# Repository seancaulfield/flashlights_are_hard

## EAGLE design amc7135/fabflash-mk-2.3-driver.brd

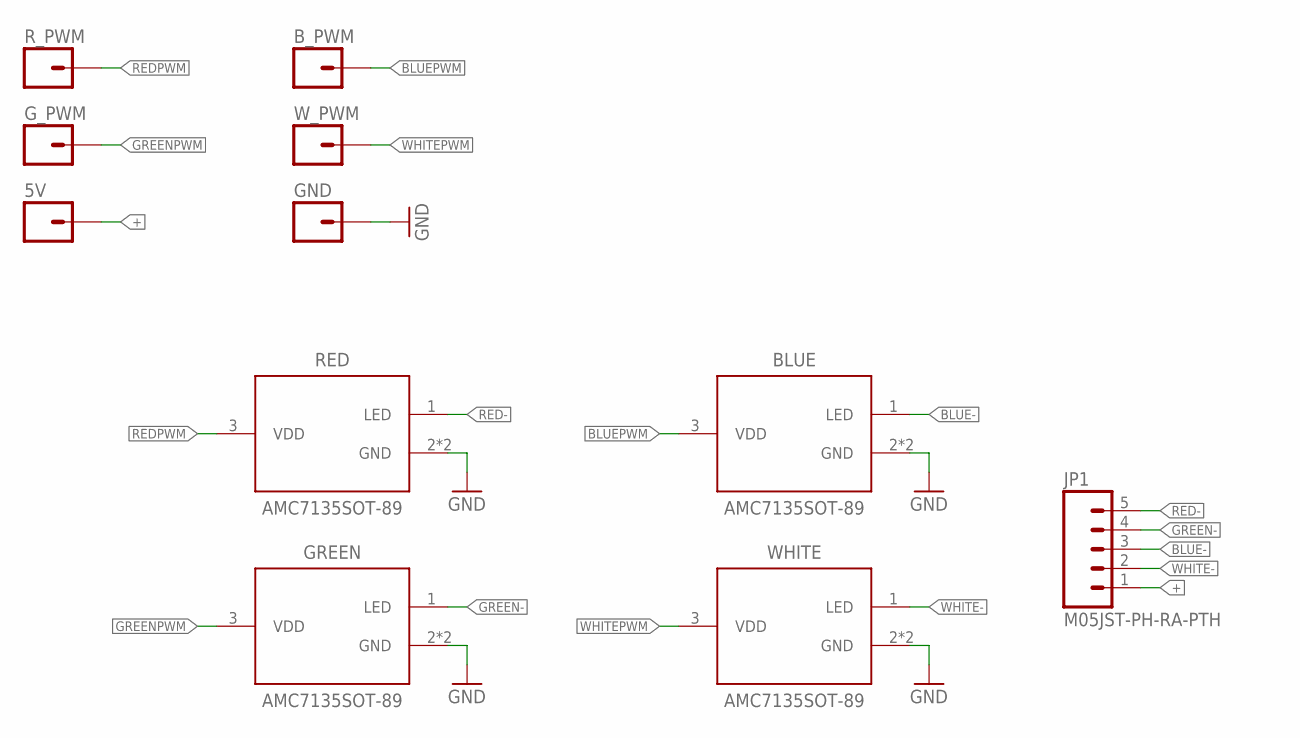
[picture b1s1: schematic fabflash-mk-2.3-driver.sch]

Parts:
5V: M01PTH-0.9MM; 1X01-0.9MM
BLUE: AMC7135SOT-89; SOT89
B_PWM: M01PTH-0.9MM; 1X01-0.9MM
GND: M01PTH-0.9MM; 1X01-0.9MM
GREEN: AMC7135SOT-89; SOT89
G_PWM: M01PTH-0.9MM; 1X01-0.9MM
JP1: M05JST-PH-RA-PTH; JST-5-PH-RA-PTH
RED: AMC7135SOT-89; SOT89
R_PWM: M01PTH-0.9MM; 1X01-0.9MM
WHITE: AMC7135SOT-89; SOT89
W_PWM: M01PTH-0.9MM; 1X01-0.9MM

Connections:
+: 5V.1, JP1.1
BLUE-: BLUE.1 (LED), JP1.3
BLUEPWM: BLUE.3 (VDD), B_PWM.1
GND: BLUE.2 (GND), BLUE.4 (GND), GND.1, GREEN.2 (GND), GREEN.4 (GND), RED.2 (GND), RED.4 (GND), WHITE.2 (GND), WHITE.4 (GND)
GREEN-: GREEN.1 (LED), JP1.4
GREENPWM: GREEN.3 (VDD), G_PWM.1
RED-: JP1.5, RED.1 (LED)
REDPWM: RED.3 (VDD), R_PWM.1
WHITE-: JP1.2, WHITE.1 (LED)
WHITEPWM: WHITE.3 (VDD), W_PWM.1

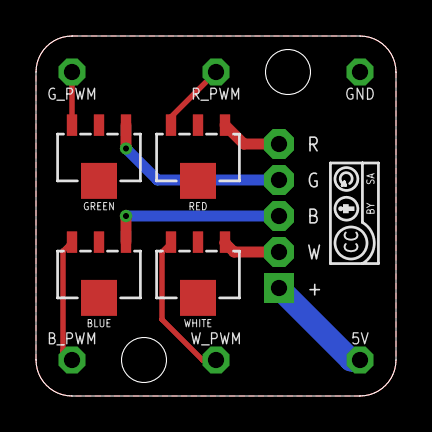
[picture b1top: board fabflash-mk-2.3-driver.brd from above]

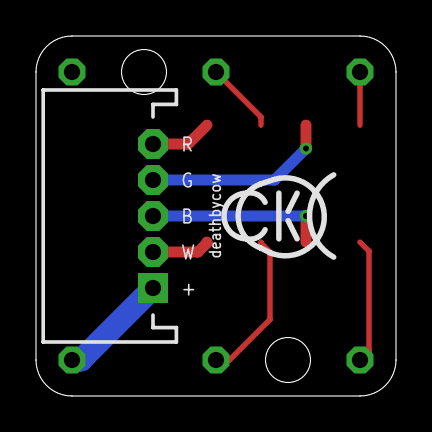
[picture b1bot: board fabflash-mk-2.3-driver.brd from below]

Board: 2 copper layers, 20.0 x 20.0 mm, 13 parts (2 on the bottom side), 10 nets.

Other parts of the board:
U$1: CC-BY-SA-4.0-NO-URL
U$2: COW_SMALL

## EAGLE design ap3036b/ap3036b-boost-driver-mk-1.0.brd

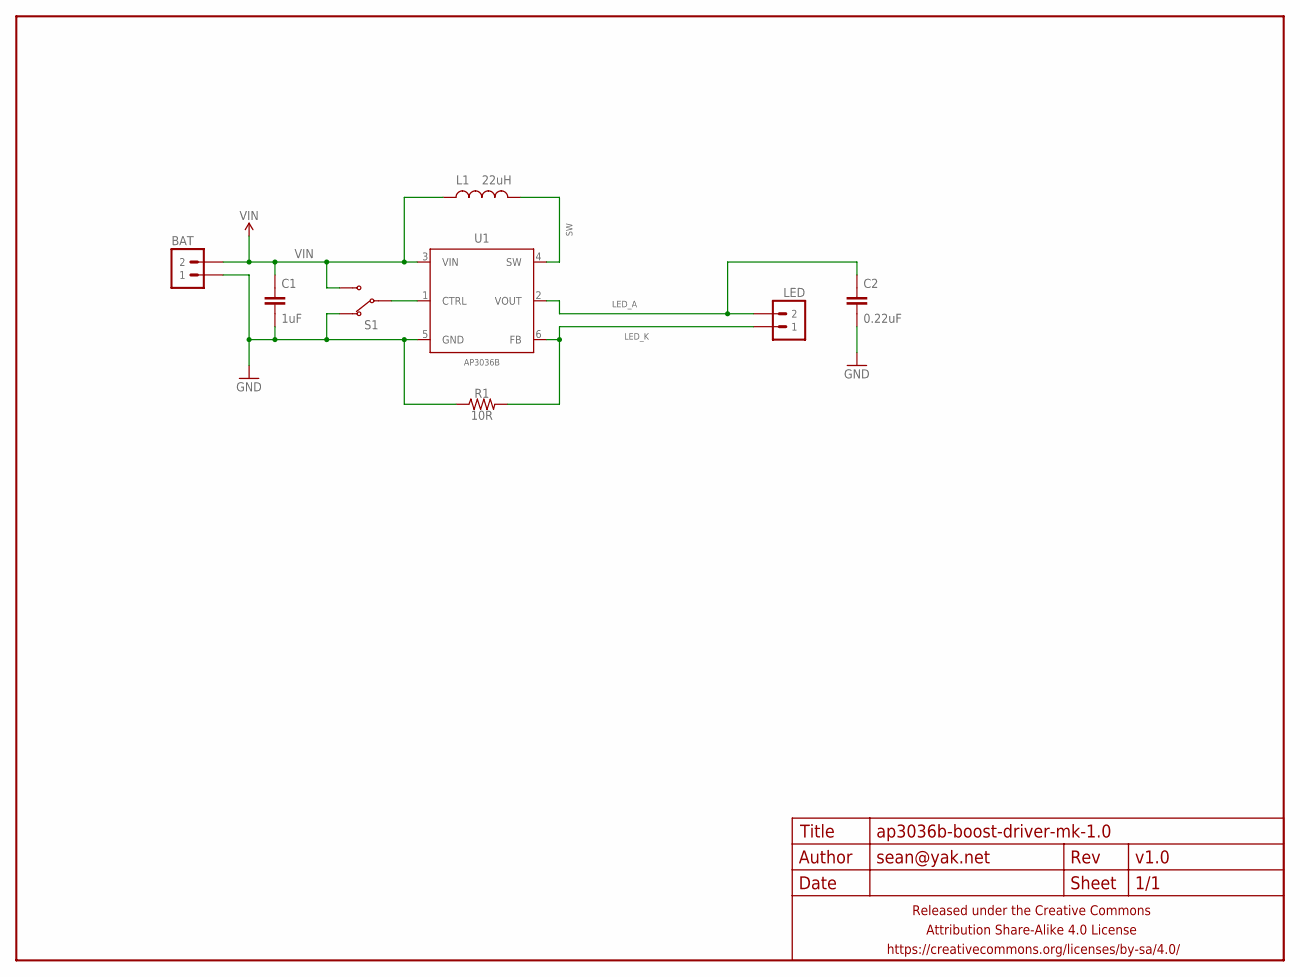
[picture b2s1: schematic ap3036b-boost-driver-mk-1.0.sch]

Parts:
BAT: M02PTH-CENTERED; 1X02-CENTER
C1: 1uF; C0603-TIGHTER
C2: 0.22uF; C0603-TIGHTER
FRAME1: FRAME-LETTERNO_PACKAGE; DUMMY
L1: 22uH; L0603
LED: M02PTH-CENTERED; 1X02-CENTER
R1: 10R; R0603-TIGHTER
S1: SWITCH-SPDTJS102011SAQN; SWITCH-SPDT-SMD-RA-JS102011SAQN
U1: AP3036B; SOT26

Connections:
GND: BAT.1, C1.2, C2.2, R1.1, S1.3 (NC), U1.5 (GND)
LED_A: C2.1, LED.2, U1.2 (VOUT)
LED_K: LED.1, R1.2, U1.6 (FB)
unnamed: S1.2 (COM), U1.1 (CTRL)
SW: L1.2, U1.4 (SW)
VIN: BAT.2, C1.1, L1.1, S1.1 (NO), U1.3 (VIN)

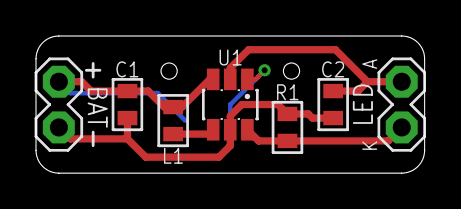
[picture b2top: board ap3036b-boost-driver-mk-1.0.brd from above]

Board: 2 copper layers, 21.6 x 7.6 mm, 9 parts (1 on the bottom side), 6 nets.

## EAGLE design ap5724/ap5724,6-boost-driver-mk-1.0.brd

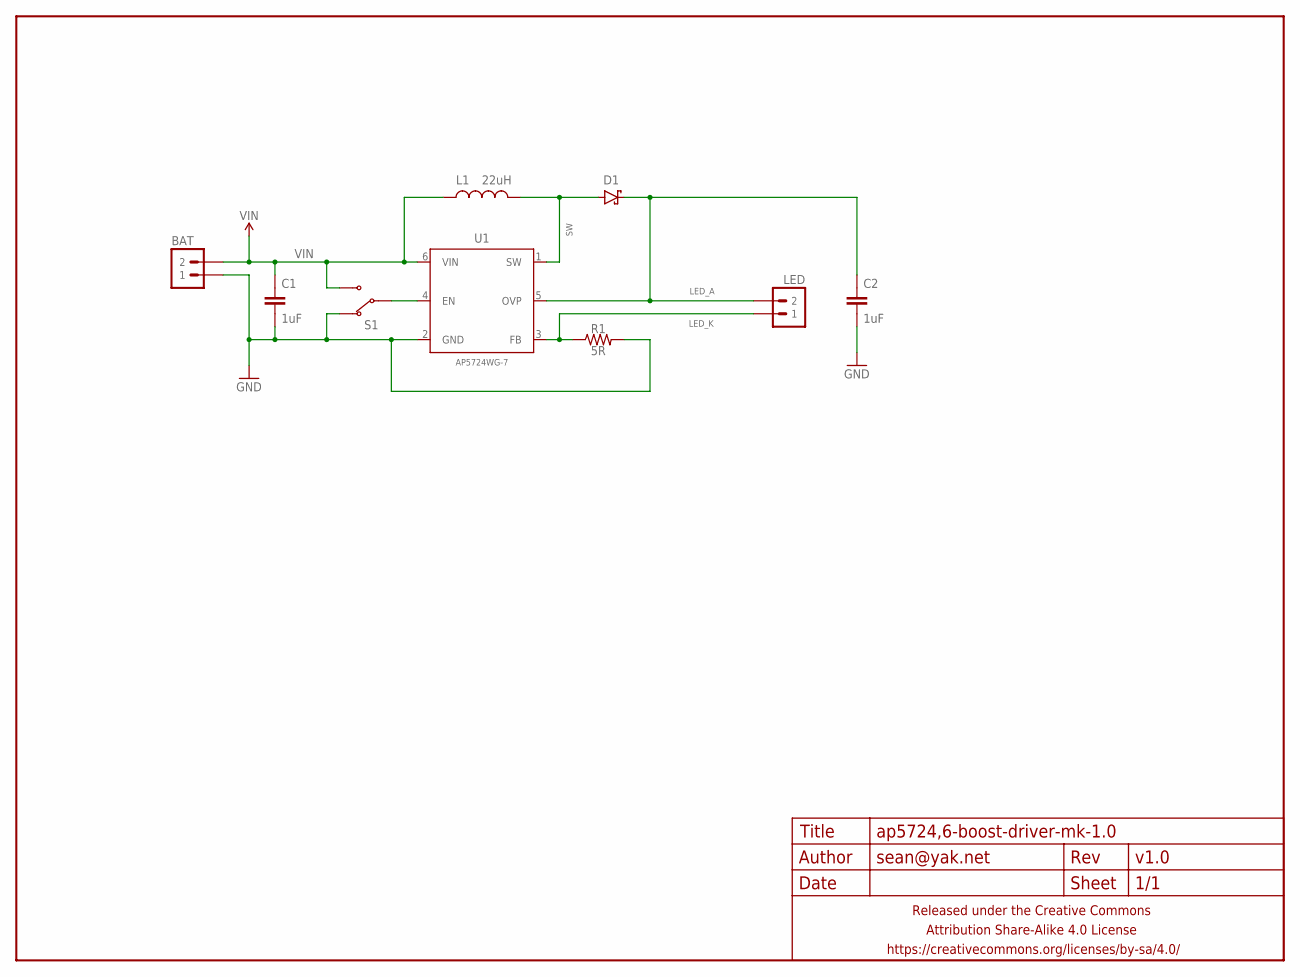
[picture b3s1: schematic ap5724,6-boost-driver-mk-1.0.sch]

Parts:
BAT: M02PTH-CENTERED; 1X02-CENTER
C1, C2: 1uF; C0603-TIGHTER
D1: DIODE-SCHOTTKYSOD323; SOD323-SCHOTTKY
FRAME1: FRAME-LETTERNO_PACKAGE; DUMMY
L1: 22uH; L0603
LED: M02PTH-CENTERED; 1X02-CENTER
R1: 5R; R0603-TIGHTER
S1: SWITCH-SPDTJS102011SAQN; SWITCH-SPDT-SMD-RA-JS102011SAQN
U1: AP5724WG-7; SOT26

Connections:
GND: BAT.1, C1.2, C2.2, R1.2, S1.3 (NC), U1.2 (GND)
LED_A: C2.1, D1.C, LED.2, U1.5 (OVP)
LED_K: LED.1, R1.1, U1.3 (FB)
unnamed: S1.2 (COM), U1.4 (EN)
SW: D1.A, L1.2, U1.1 (SW)
VIN: BAT.2, C1.1, L1.1, S1.1 (NO), U1.6 (VIN)

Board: 2 copper layers, 10 parts (1 on the bottom side), 6 nets, no tracks yet.

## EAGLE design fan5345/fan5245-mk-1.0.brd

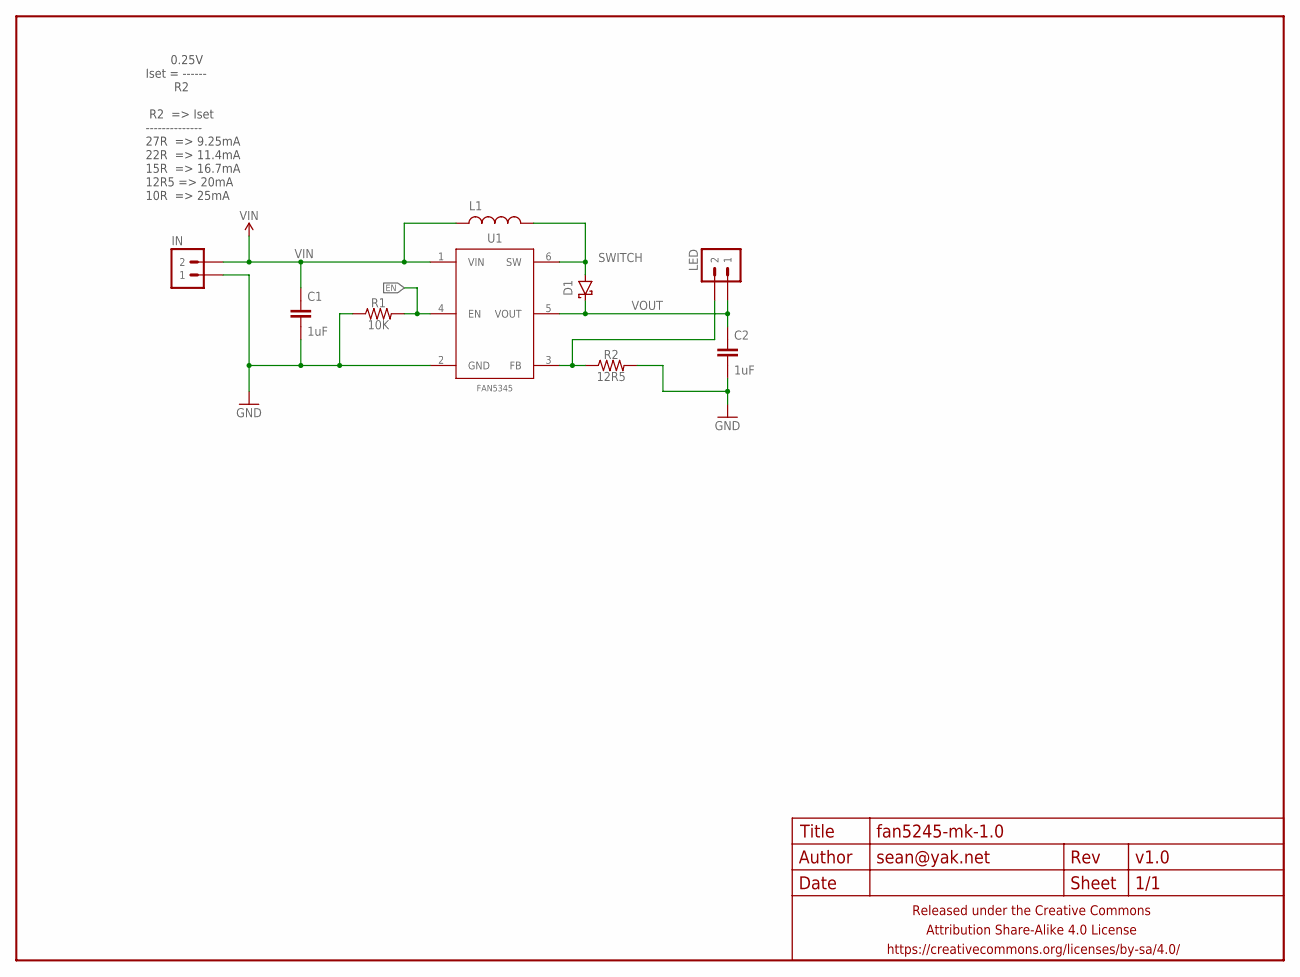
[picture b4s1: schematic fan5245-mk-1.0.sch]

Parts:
C1, C2: 1uF; C0603-TIGHTER
D1: DIODE-SCHOTTKYSOD323; SOD323-SCHOTTKY
FRAME1: FRAME-LETTERNO_PACKAGE; DUMMY
IN: M02PTH-CENTERED-R+; 1X02-CENTER-R+
L1: 10uH; L0603
LED: M02PTH-CENTERED-L+; 1X02-CENTER-L+
R1: 10K; R0603-TIGHTER
R2: 12R5; R0603-TIGHTER
U1: FAN5345; SOT23-6

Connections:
EN: R1.2, U1.4 (EN)
GND: C1.2, C2.2, IN.1, R1.1, R2.2, U1.2 (GND)
unnamed: LED.2, R2.1, U1.3 (FB)
SWITCH: D1.A, L1.2, U1.6 (SW)
VIN: C1.1, IN.2, L1.1, U1.1 (VIN)
VOUT: C2.1, D1.C, LED.1, U1.5 (VOUT)

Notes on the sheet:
0.25V Iset = ------ R2 R2 => Iset -------------- 27R => 9.25mA 22R => 11.4mA 15R => 16.7mA 12R5 => 20mA 10R => 25mA

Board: 2 copper layers, 10 parts (0 on the bottom side), 6 nets, no tracks yet.

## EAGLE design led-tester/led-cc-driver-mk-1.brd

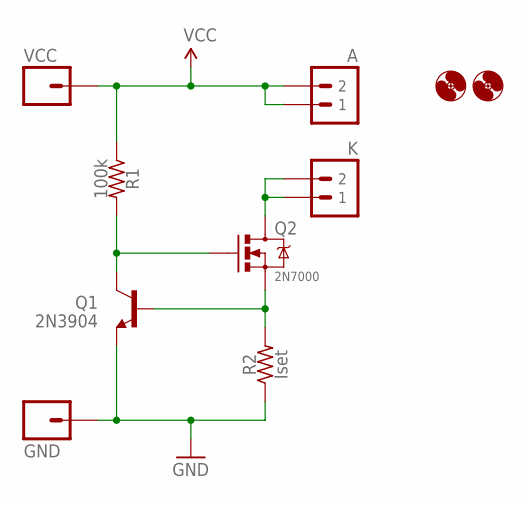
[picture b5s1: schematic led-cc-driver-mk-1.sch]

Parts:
A: M02PTH; 1X02
GND: M01PTH; 1X01
H1, H2: HOLE#2; HOLE-#2
K: M02PTH; 1X02
Q1: 2N3904; TO-92-AMMO
Q2: 2N7000; TO-92-AMMO
R1: 100k; RESISTOR-AXIAL-PTH-7.62MM
R2: Iset; RESISTOR-AXIAL-PTH-7.62MM
VCC: M01PTH; 1X01

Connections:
GND: GND.1, Q1.1 (E), R2.P$1 (1)
unnamed: Q1.2 (B), Q2.1 (S), R2.P$2 (2)
unnamed: Q1.3 (C), Q2.2 (G), R1.P$2 (2)
unnamed: K.1, K.2, Q2.3 (D)
VCC: A.1, A.2, R1.P$1 (1), VCC.1

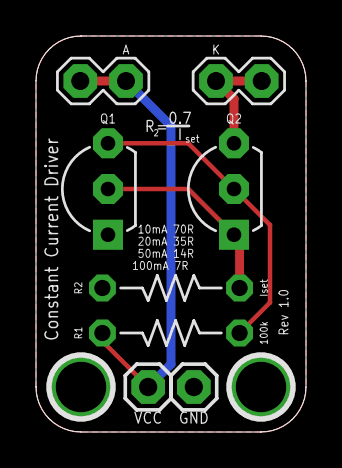
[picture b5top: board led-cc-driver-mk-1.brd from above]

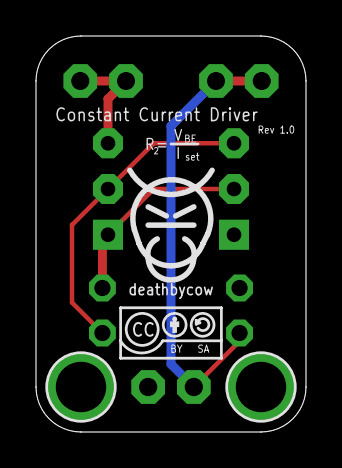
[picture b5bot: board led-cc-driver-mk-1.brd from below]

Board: 2 copper layers, 15.0 x 22.0 mm, 12 parts (2 on the bottom side), 5 nets.

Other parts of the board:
U$1: COW_SMALL
U$4: CC-BY-SA-4.0-NO-URL

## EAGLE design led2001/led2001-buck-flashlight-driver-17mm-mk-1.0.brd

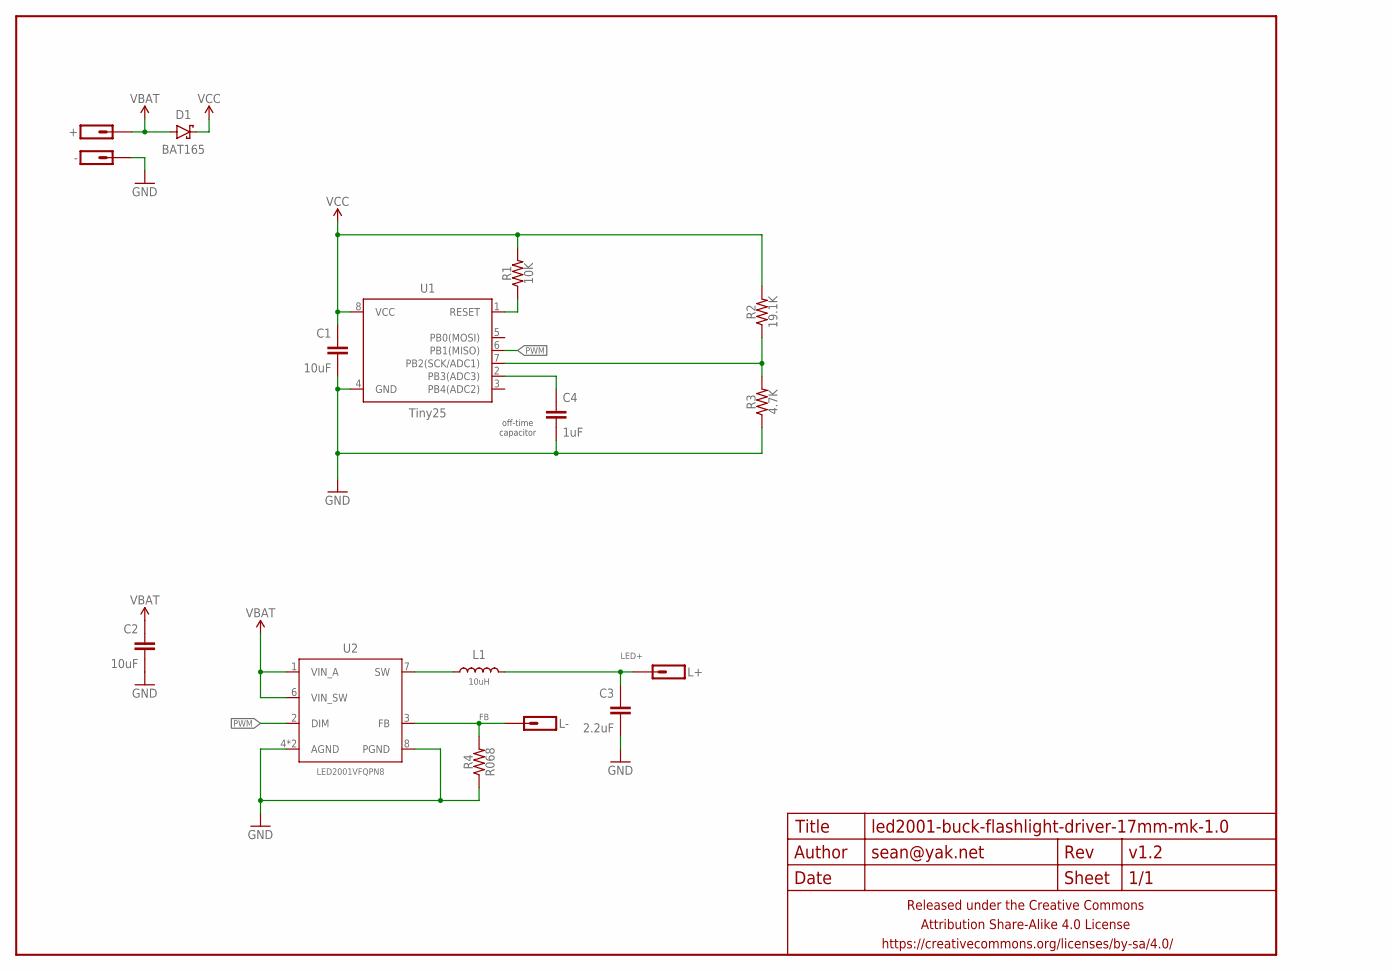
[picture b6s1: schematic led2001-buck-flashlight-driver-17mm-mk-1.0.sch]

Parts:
+: M01PTH-1MM-CIR-NS; 1X01-1MM-CIR-NS
-: M01NOT-A-VIA-NOPE; 1X01_NOSILK_NOSTOP
C1, C2: 10uF; C0603-TIGHTER
C3: 2.2uF; C0603-TIGHTER
C4: 1uF; C0402
D1: BAT165; SOD323-SCHOTTKY
FRAME1: FRAME-LETTERNO_PACKAGE; DUMMY
L1: 10uH; XAL40X0
L+: M01PTH-1MM-CIR-NS; 1X01-1MM-CIR-NS
L-: M01PTH-1MM-CIR-NS; 1X01-1MM-CIR-NS
R1: 10K; R0402
R2: 19.1K; R0603-TIGHTER
R3: 4.7K; R0603-TIGHTER
R4: R068; R0805-TIGHTER
U1: Tiny25; SO08-SKINNYPADS
U2: LED2001VFQPN8; VFQFPN8-4X4

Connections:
FB: L-.1, R4.2, U2.3 (FB)
GND: -.P$1, C1.2, C2.2, C3.2, C4.2, R3.1, R4.1, U1.4 (GND), U2.4 (AGND), U2.8 (PGND), U2.9 (AGND)
LED+: C3.1, L1.P$2 (2), L+.1
unnamed: L1.P$1 (1), U2.7 (SW)
unnamed: R1.1, U1.1 (RESET)
unnamed: R2.1, R3.2, U1.7 (PB2(SCK/ADC1))
unnamed: C4.1, U1.2 (PB3(ADC3))
PWM: U1.6 (PB1(MISO)), U2.2 (DIM)
VBAT: +.1, C2.1, D1.A, U2.1 (VIN_A), U2.6 (VIN_SW)
VCC: C1.1, D1.C, R1.2, R2.2, U1.8 (VCC)

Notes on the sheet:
off-time capacitor

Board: 2 copper layers, 17 parts (3 on the bottom side), 10 nets, no tracks yet.

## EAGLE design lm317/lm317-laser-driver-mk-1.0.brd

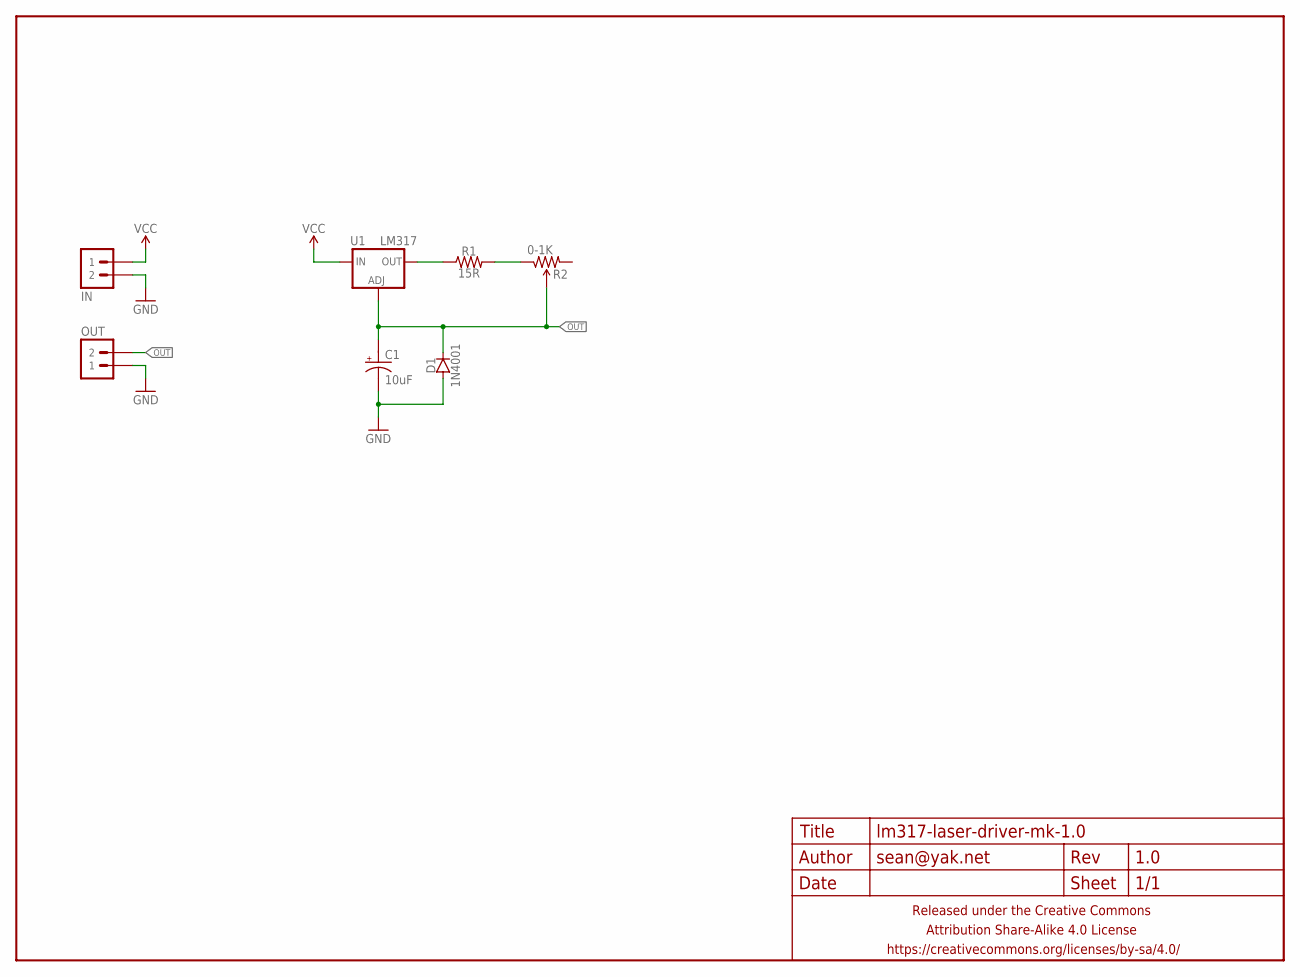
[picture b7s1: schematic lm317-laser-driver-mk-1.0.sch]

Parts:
C1: 10uF; E2,5-6
D1: 1N4001; DIODE-10.16MM-NOSYMBOL
FRAME1: FRAME-LETTERNO_PACKAGE; DUMMY
IN: M02PTH-CENTERED-R+; 1X02-CENTER-R+
OUT: M02PTH-CENTERED-R+; 1X02-CENTER-R+
R1: 15R; RESISTOR-AXIAL-PTH-10.16MM
R2: 0-1K; TRIM_POT_PTH2
U1: LM317; TO220-THERMPAD

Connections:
GND: C1.-, D1.A, IN.2, OUT.1
unnamed: R1.P$2 (2), R2.1 (CCW)
unnamed: R1.P$1 (1), U1.2@1 (OUT), U1.2@2 (OUT)
OUT: C1.+, D1.C, OUT.2, R2.2 (WIPER), U1.1 (ADJ)
VCC: IN.1, U1.3 (IN)

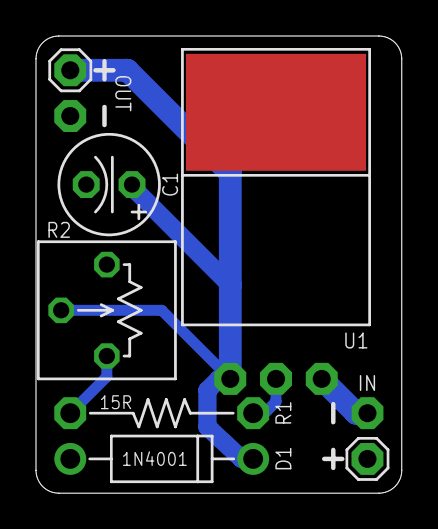
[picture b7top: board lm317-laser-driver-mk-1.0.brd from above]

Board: 2 copper layers, 20.3 x 25.4 mm, 9 parts (1 on the bottom side), 5 nets.

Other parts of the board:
U$1: COW

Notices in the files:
parts and their libraries:
a_parts: Released under the Creative Commons Attribution Share-Alike 4.0 License
a_parts: https://creativecommons.org/licenses/by-sa/4.0
a_parts: Released under the Creative Commons
